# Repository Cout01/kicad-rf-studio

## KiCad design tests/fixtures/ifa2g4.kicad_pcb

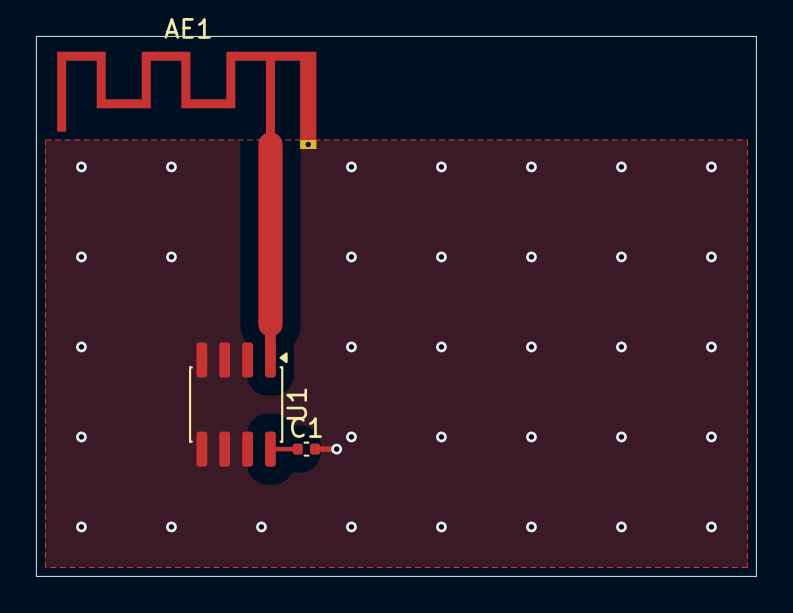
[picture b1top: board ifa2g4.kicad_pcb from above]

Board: 2 copper layers, 40.0 x 30.0 mm, 3 parts (0 on the bottom side), 3 nets.

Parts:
AE1: Texas_SWRA117D_2.4GHz_Left
C1: 100nF; C_0402_1005Metric
U1: RFIC; SOIC-8_3.9x4.9mm_P1.27mm

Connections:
GND: AE1.2, C1.2, U1.2, U1.3, U1.4, U1.5, U1.6, U1.7
RF: AE1.1, U1.1
VDD: C1.1, U1.8

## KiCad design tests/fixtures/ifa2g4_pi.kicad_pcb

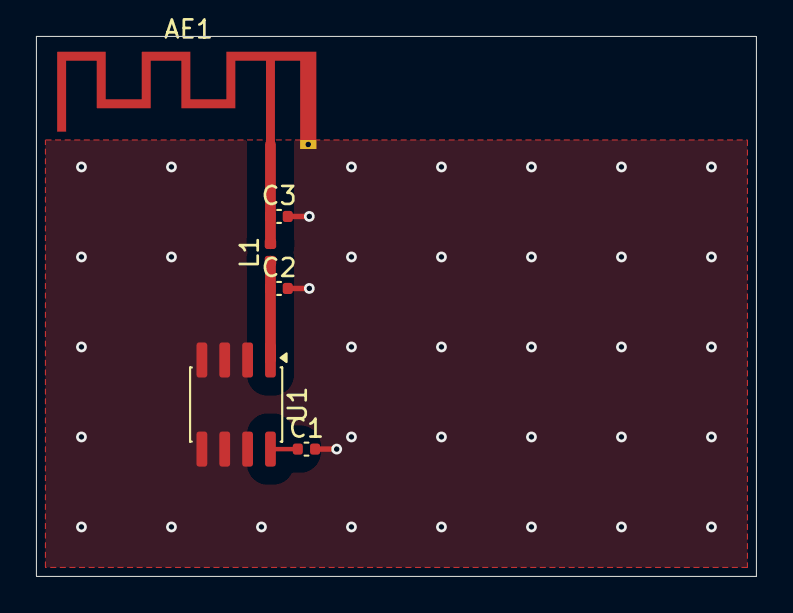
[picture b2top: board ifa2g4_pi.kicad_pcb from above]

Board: 2 copper layers, 40.0 x 30.0 mm, 6 parts (0 on the bottom side), 4 nets.

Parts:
AE1: Texas_SWRA117D_2.4GHz_Left
C1: 100nF; C_0402_1005Metric
C2, C3: 1pF; C_0402_1005Metric
L1: 2.7nH; L_0402_1005Metric
U1: RFIC; SOIC-8_3.9x4.9mm_P1.27mm

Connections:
GND: AE1.2, C1.2, C2.2, C3.2, U1.2, U1.3, U1.4, U1.5, U1.6, U1.7
RF: AE1.1, C3.1, L1.2
RF_A: C2.1, L1.1, U1.1
VDD: C1.1, U1.8

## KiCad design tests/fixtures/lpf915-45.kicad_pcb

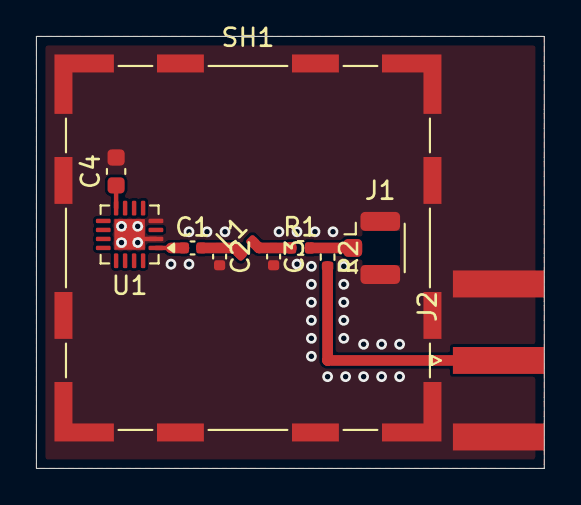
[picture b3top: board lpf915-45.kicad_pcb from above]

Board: 2 copper layers, 28.2 x 24.0 mm, 11 parts (0 on the bottom side), 7 nets.

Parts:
C1: 100pF; C_0402_1005Metric
C2, C3: 3.3pF; C_0402_1005Metric
C4: 10uF/16V; C_0603_1608Metric
J1: U.FL; U.FL_Hirose_U.FL-R-SMT-1_Vertical
J2: SMA; SMA_Amphenol_132289_EdgeMount
L1: 15nH; L_0402_1005Metric
R1, R2: 0R; R_0402_1005Metric
SH1: SHIELD; Wuerth_36103205_20x20mm
U1: RFIC; QFN-16-1EP_3x3mm_P0.5mm_EP1.7x1.7mm

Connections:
GND: C2.2, C3.2, C4.2, J1.2, J2.2, SH1.1, U1.2, U1.4, U1.17
RF_A: C1.1, U1.1
RF_B: C1.2, C2.1, L1.1
RF_C: C3.1, L1.2, R1.1
RF_OUT: J1.1, R1.2, R2.1
RF_SMA: J2.1, R2.2
VDD: C4.1, U1.8
